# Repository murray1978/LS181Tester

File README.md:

# LS181Tester
 Tester for 74LS181

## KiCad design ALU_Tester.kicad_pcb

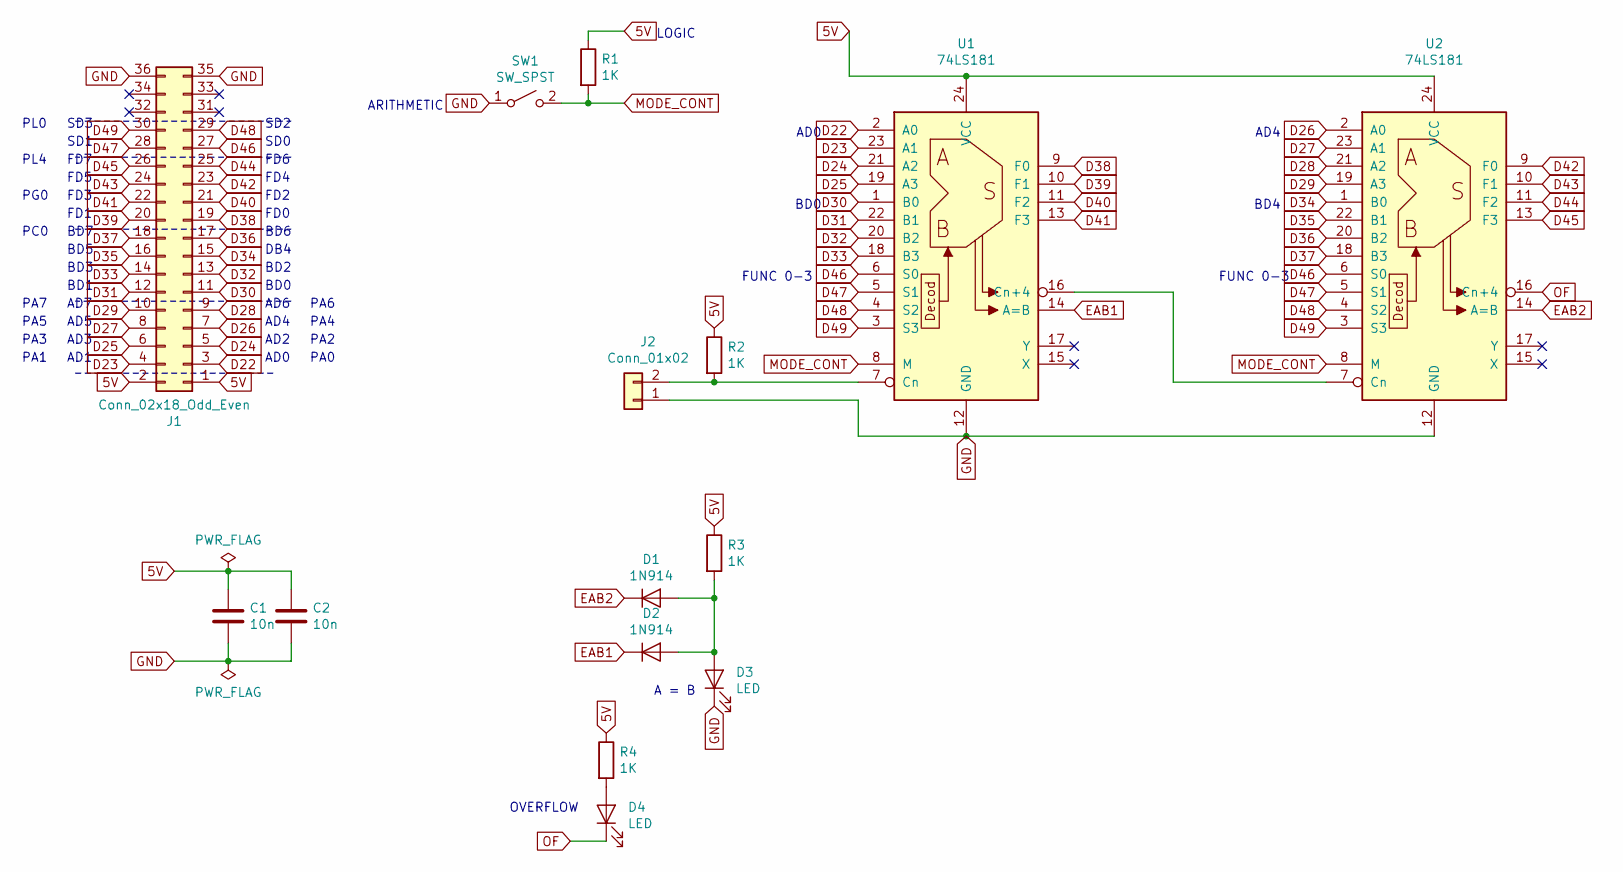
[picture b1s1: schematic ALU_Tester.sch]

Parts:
C1, C2: 10n; C_Rect_L7.0mm_W2.0mm_P5.00mm
D1, D2: 1N914; D_DO-35_SOD27_P7.62mm_Horizontal
D3, D4: LED; LED_D5.0mm
J1: Conn_02x18_Odd_Even; PinHeader_2x18_P2.54mm_Vertical
J2: Conn_01x02; PinHeader_1x02_P2.54mm_Vertical
R1, R2, R3, R4: 1K; R_Axial_DIN0207_L6.3mm_D2.5mm_P10.16mm_Horizontal
SW1: SW_SPST; PinSocket_1x02_P2.54mm_Vertical
U1, U2: 74LS181; DIP-24_W15.24mm_LongPads

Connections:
5V: C1.1, C2.1, J1.1, J1.2, R1.1, R2.1, R3.1, R4.1, U1.24 (VCC), U2.24 (VCC)
D22: J1.3, U1.2 (A0)
D23: J1.4, U1.23 (A1)
D24: J1.5, U1.21 (A2)
D25: J1.6, U1.19 (A3)
D26: J1.7, U2.2 (A0)
D27: J1.8, U2.23 (A1)
D28: J1.9, U2.21 (A2)
D29: J1.10, U2.19 (A3)
D30: J1.11, U1.1 (B0)
D31: J1.12, U1.22 (B1)
D32: J1.13, U1.20 (B2)
D33: J1.14, U1.18 (B3)
D34: J1.15, U2.1 (B0)
D35: J1.16, U2.22 (B1)
D36: J1.17, U2.20 (B2)
D37: J1.18, U2.18 (B3)
D38: J1.19, U1.9 (F0)
D39: J1.20, U1.10 (F1)
D40: J1.21, U1.11 (F2)
D41: J1.22, U1.13 (F3)
D42: J1.23, U2.9 (F0)
D43: J1.24, U2.10 (F1)
D44: J1.25, U2.11 (F2)
D45: J1.26, U2.13 (F3)
D46: J1.27, U1.6 (S0), U2.6 (S0)
D47: J1.28, U1.5 (S1), U2.5 (S1)
D48: J1.29, U1.4 (S2), U2.4 (S2)
D49: J1.30, U1.3 (S3), U2.3 (S3)
EAB1: D2.1 (K), U1.14 (A=B)
EAB2: D1.1 (K), U2.14 (A=B)
GND: C1.2, C2.2, D3.1 (K), J1.35, J1.36, J2.1, SW1.1 (A), U1.12 (GND), U2.12 (GND)
MODE_CONT: R1.2, SW1.2 (B), U1.8 (M), U2.8 (M)
unnamed: D1.2 (A), D2.2 (A), D3.2 (A), R3.2
unnamed: D4.2 (A), R4.2
unnamed: J2.2, R2.2, U1.7 (Cn)
unnamed: U1.16 (Cn+4), U2.7 (Cn)
OF: D4.1 (K), U2.16 (Cn+4)

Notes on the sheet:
AD0
BD0
AD4
BD4
FUNC 0-3
LOGIC
ARITHMETIC
FD0
SD0
AD2
AD6
BD2
DB4
BD6
FD2
FD4
FD6
AD1
AD3
AD5
AD7
BD1
BD3
BD5
BD7
FD1
FD3
FD5
FD7
SD2
SD3
SD1
A = B
OVERFLOW
PA1
PA0
PA3
PA5
PA7
PA2

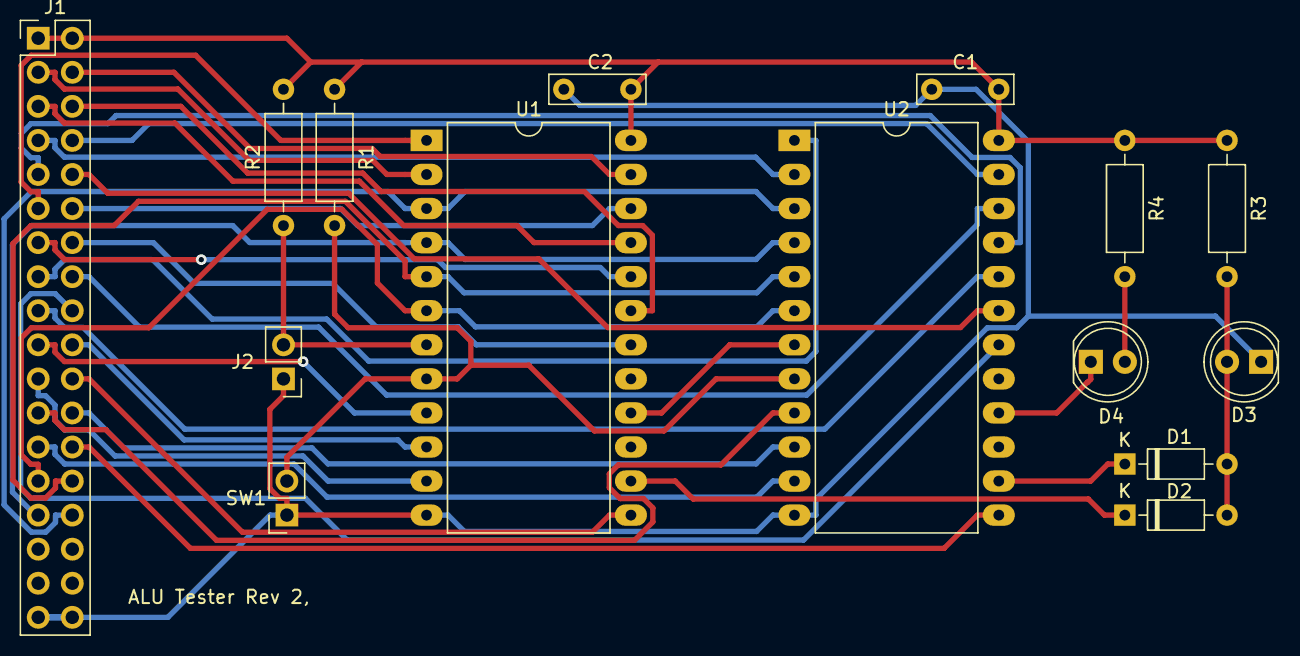
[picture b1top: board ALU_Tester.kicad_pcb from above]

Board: 2 copper layers, 15 parts (0 on the bottom side), 38 nets.

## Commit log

2020-04-19 Initialise repo
    Initialise repo
2020-04-30 Upadate board
    Update of board, fixed 24 pin ic size, adjusted board size.
2020-04-30 Update LS181Tester.ino
    Adding tester code
2020-05-28 Daily Update
    Added code to project.
